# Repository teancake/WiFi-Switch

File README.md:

# WiFi-Switch
Schematic and PCB design of a WiFi switch.

### Description ###
This WiFi switch module utilises the ESP-12E/F adaptor.

### Features ###

### The Finished Board ###

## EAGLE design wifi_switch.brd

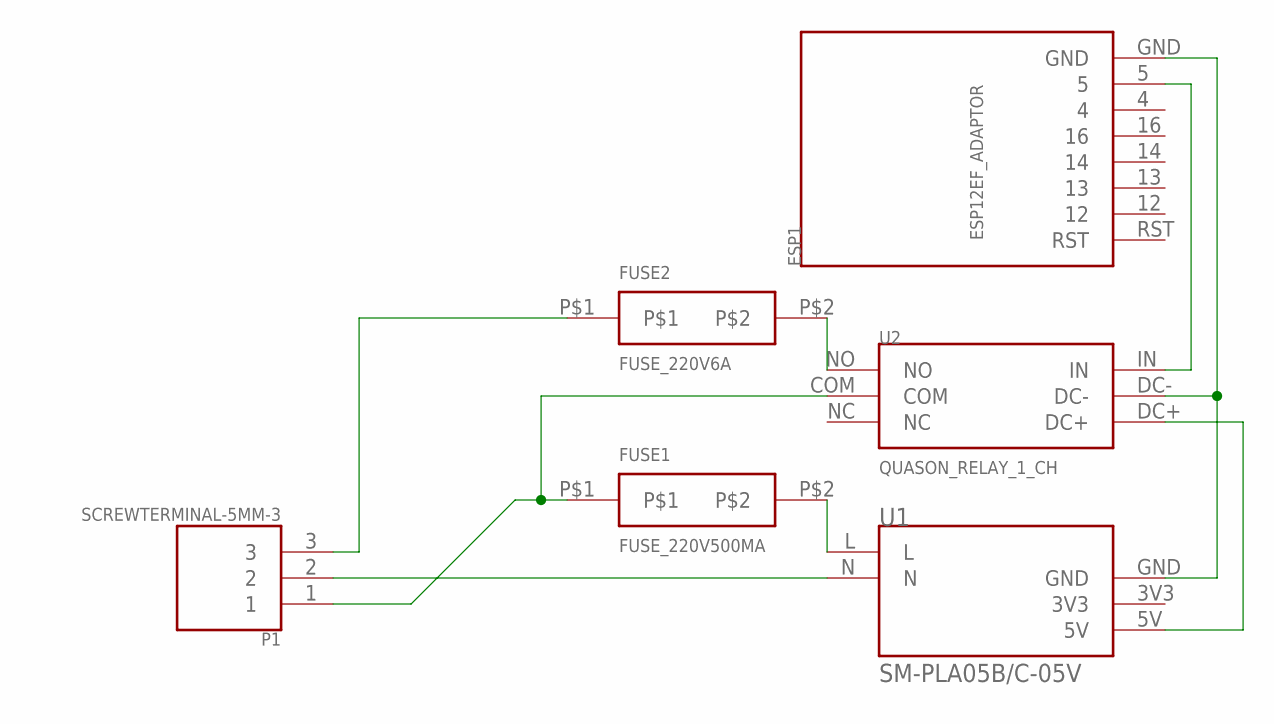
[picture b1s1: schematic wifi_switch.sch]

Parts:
ESP1: ESP12EF_ADAPTOR
FUSE1: FUSE_220V500MA; FUSE_220V_5X20MM
FUSE2: FUSE_220V6A; FUSE_220V_5X20MM
P1: SCREWTERMINAL-5MM-3
U1: SM-PLA05B/C-05V
U2: QUASON_RELAY_1_CH

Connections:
unnamed: P1.2, U1.N
unnamed: FUSE1.P$2, U1.L
unnamed: FUSE1.P$1, P1.1, U2.COM
unnamed: FUSE2.P$1, P1.3
unnamed: U1.5V, U2.DC+
unnamed: FUSE2.P$2, U2.NO
unnamed: ESP1.GND, U1.GND, U2.DC-
unnamed: ESP1.5, U2.IN

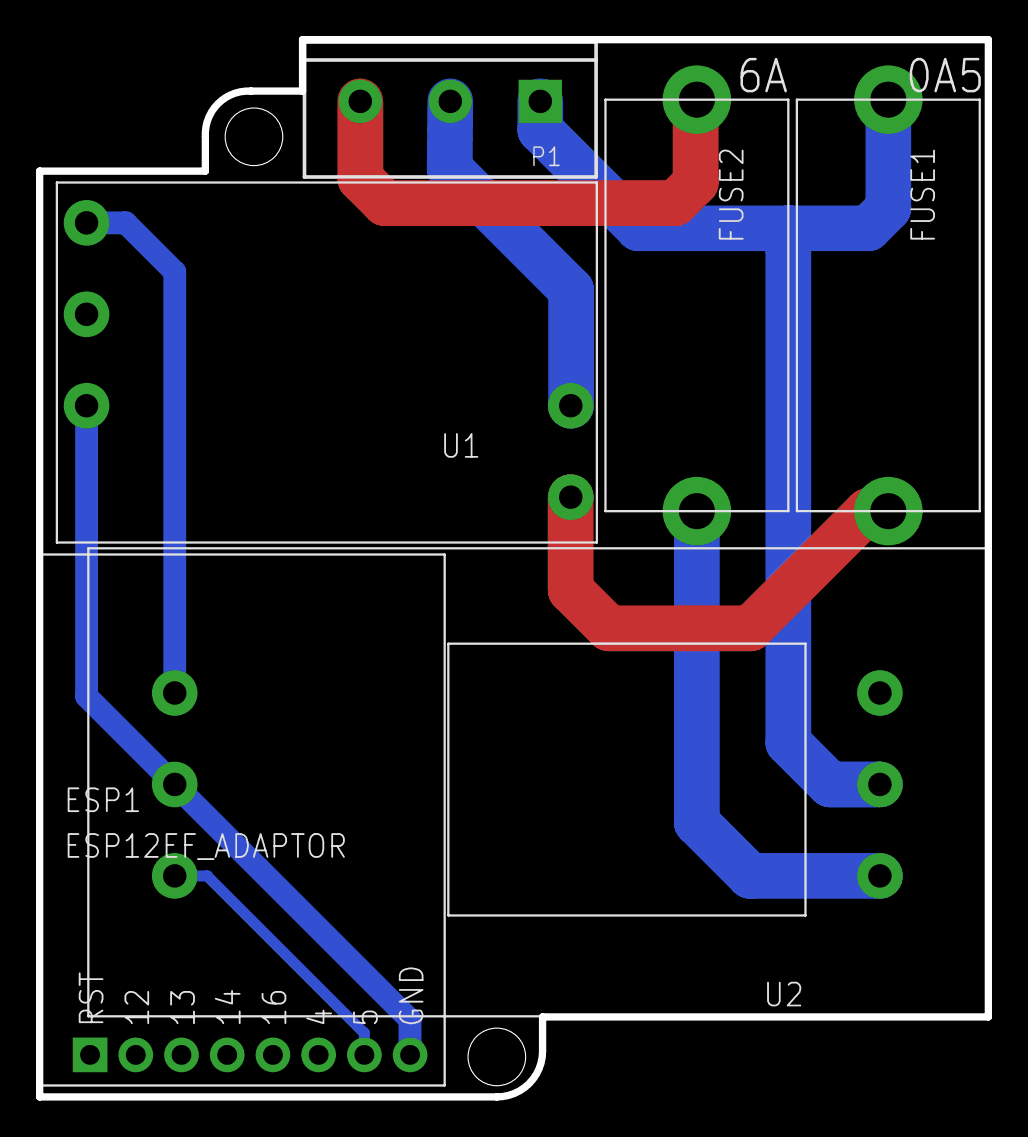
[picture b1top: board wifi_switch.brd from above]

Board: 2 copper layers, 52.7 x 58.7 mm, 6 parts (0 on the bottom side), 8 nets.

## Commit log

2017-01-17 initial release
2017-01-17 Update README.md
    update the README file, more contents still need to be written.
